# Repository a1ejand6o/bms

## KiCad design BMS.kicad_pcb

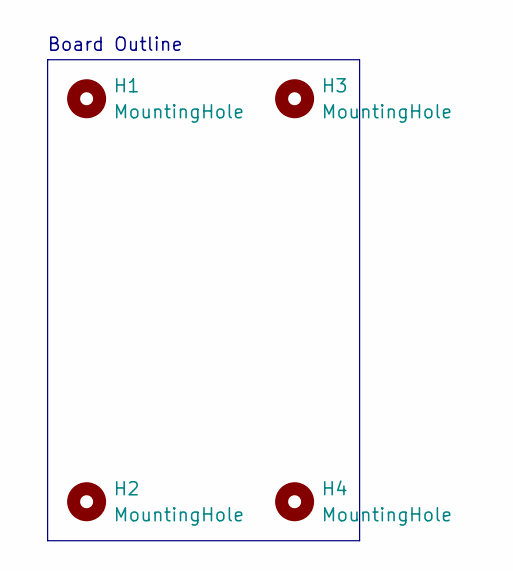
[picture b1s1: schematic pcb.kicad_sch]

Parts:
H1, H2, H3, H4: MountingHole; MountingHole_2.2mm_M2_Pad_TopBottom

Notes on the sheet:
Board Outline

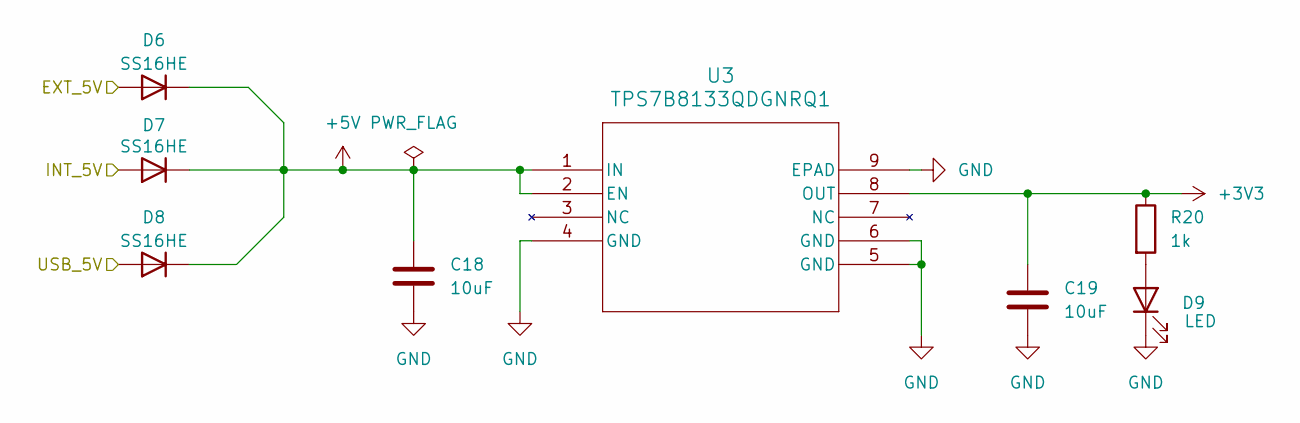
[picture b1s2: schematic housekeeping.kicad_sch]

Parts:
C18, C19: 10uF; C_0805_2012Metric; Mfr P/N GRM21BR61H106KE43L
D6, D7, D8: SS16HE; D_SOD-323F; Mfr P/N SS16HE
D9: LED; LED_0603_1608Metric; Mfr P/N SML-E12P8WT86
R20: 1k; R_0603_1608Metric; Mfr P/N AC0603FR-071KL
U3: TPS7B8133QDGNRQ1; VSSOP8_DGN_TEX; Mfr P/N TPS7B8133QDGNRQ1

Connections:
+3V3: C19.1, R20.1, U3.8 (OUT); also elsewhere on the board
+5V: C18.1, D6.1 (K), D7.1 (K), D8.1 (K), U3.1 (IN), U3.2 (EN); also elsewhere on the board
/main/EXT_5V: D6.2 (A); also elsewhere on the board
/main/INT_5V: D7.2 (A); also elsewhere on the board
/main/V_USB: D8.2 (A); also elsewhere on the board
GND: C18.2, C19.2, D9.1 (K), U3.4 (GND), U3.5 (GND), U3.6 (GND), U3.9 (EPAD); also elsewhere on the board
unnamed: D9.2 (A), R20.2

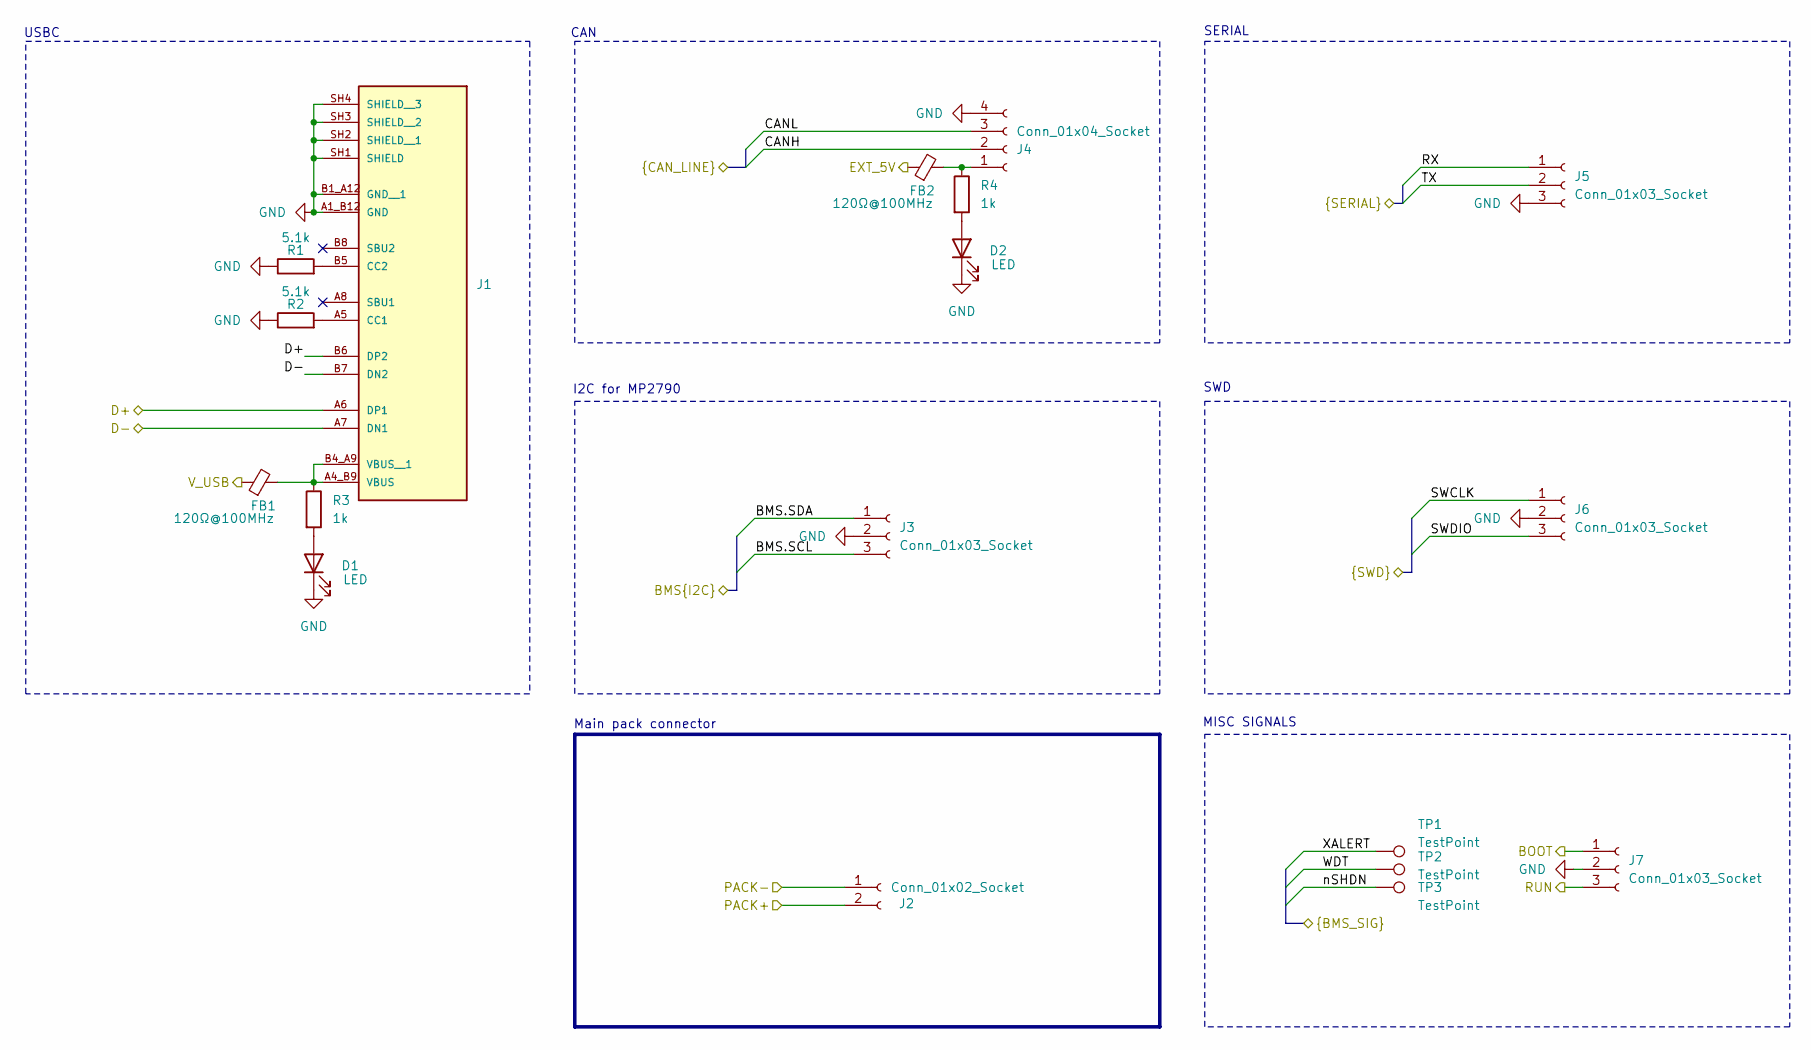
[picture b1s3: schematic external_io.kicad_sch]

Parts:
D1, D2: LED; LED_0603_1608Metric; Mfr P/N SML-E12P8WT86
FB1, FB2: 120Ω@100MHz; L_0603_1608Metric; Mfr P/N BLM18PG121SN1D
J1: UJ20-C-H-G-SMT-1-P16-TR; SAMESKY_UJ20-C-H-G-SMT-1-P16-TR; PARTREV 1.0
J2: Conn_01x02_Socket; AMASS_XT30PW-F_1x02_P2.50mm_Horizontal; Mfr P/N XT30PW-F20.G.Y
J3, J5, J6, J7: Conn_01x03_Socket; PinHeader_1x03_P2.54mm_Vertical; Mfr P/N 2.54-1*3PPin
J4: Conn_01x04_Socket; JST_GH_SM04B-GHS-TB_1x04-1MP_P1.25mm_Horizontal; Mfr P/N SM04B-GHS-TB
R1, R2: 5.1k; R_0603_1608Metric; Mfr P/N AC0603FR-075K1L
R3, R4: 1k; R_0603_1608Metric; Mfr P/N AC0603FR-071KL
TP1, TP2, TP3: TestPoint; Harwin TP; Mfr P/N S2761-46R

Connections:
/main/BMS/PACK-: J2.1; also elsewhere on the board
/main/BMS/SCL: J3.3; also elsewhere on the board
/main/BMS/SDA: J3.1; also elsewhere on the board
/main/CAN/CANH: J4.2; also elsewhere on the board
/main/CAN/CANL: J4.3; also elsewhere on the board
/main/EXT_5V: FB2.1; also elsewhere on the board
/main/PACK+: J2.2; also elsewhere on the board
/main/V_USB: FB1.1; also elsewhere on the board
/main/WDT: TP2.1; also elsewhere on the board
/main/XALERT: TP1.1; also elsewhere on the board
/main/external_io/BOOT: J7.1; also elsewhere on the board
/main/external_io/D+: J1.A6 (DP1), J1.B6 (DP2); also elsewhere on the board
/main/external_io/D-: J1.A7 (DN1), J1.B7 (DN2); also elsewhere on the board
/main/external_io/RUN: J7.3; also elsewhere on the board
/main/external_io/RX: J5.1; also elsewhere on the board
/main/external_io/SWCLK: J6.1; also elsewhere on the board
/main/external_io/SWDIO: J6.3; also elsewhere on the board
/main/external_io/TX: J5.2; also elsewhere on the board
/main/nSHDN: TP3.1; also elsewhere on the board
GND: D1.1 (K), D2.1 (K), J1.A1_B12 (GND), J1.B1_A12 (GND__1), J1.SH1 (SHIELD), J1.SH2 (SHIELD__1), J1.SH3 (SHIELD__2), J1.SH4 (SHIELD__3), J3.2, J4.4, J5.3, J6.2, J7.2, R1.1, R2.1; also elsewhere on the board
unnamed: D1.2 (A), R3.2
unnamed: D2.2 (A), R4.2
unnamed: J1.A5 (CC1), R2.2
unnamed: J1.B5 (CC2), R1.2
unnamed: FB1.2, J1.A4_B9 (VBUS), J1.B4_A9 (VBUS__1), R3.1
unnamed: FB2.2, J4.1, R4.1

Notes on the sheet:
I2C for MP2790
SERIAL
SWD
USBC
Main pack connector
MISC SIGNALS
CAN

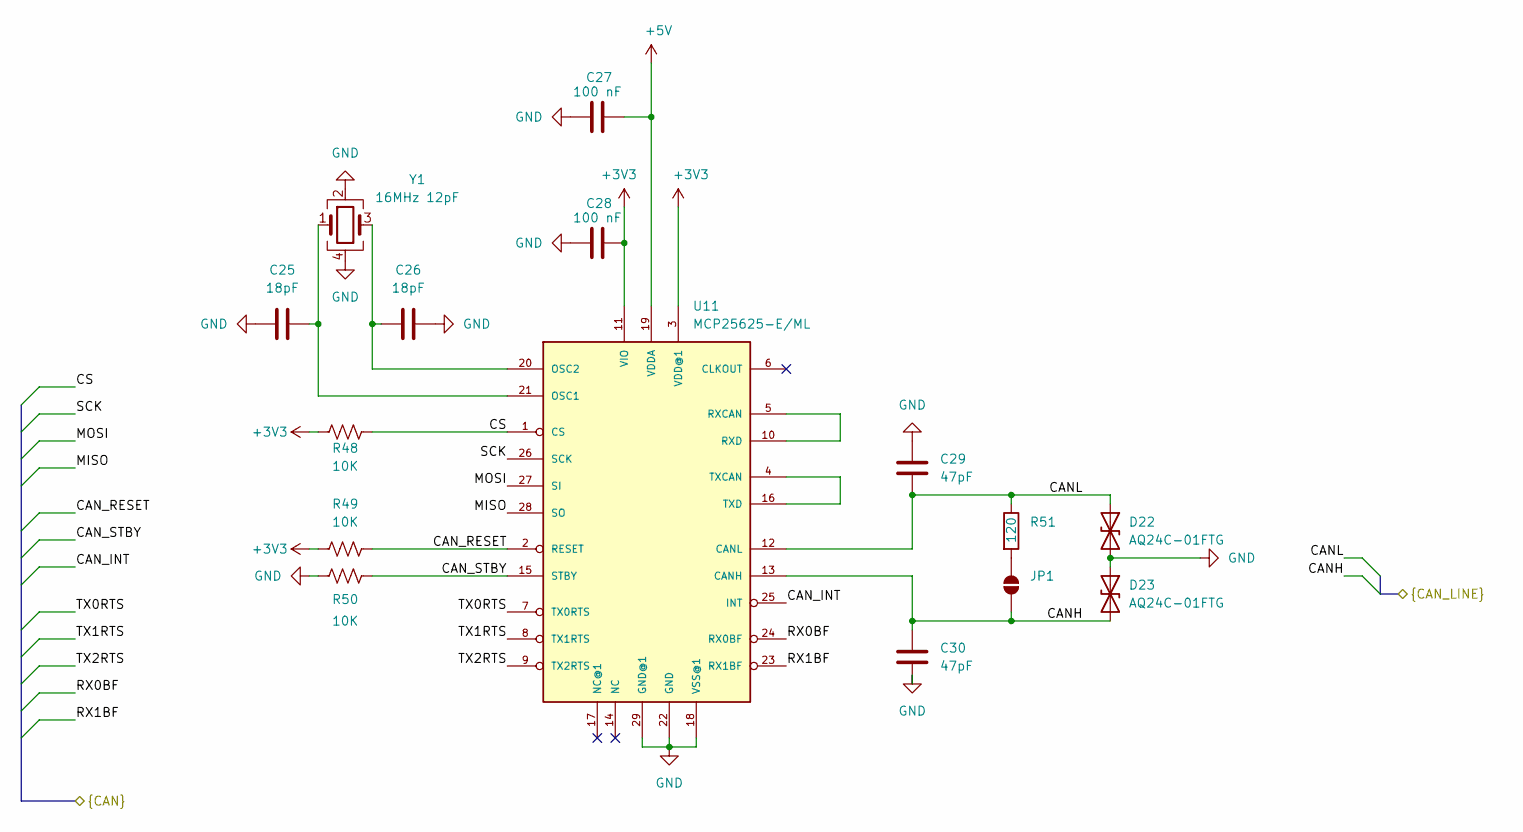
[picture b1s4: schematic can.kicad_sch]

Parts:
C25: 18pF; C_0603_1608Metric; Mfr P/N CL10C180JB8NNNC; LCSC Part C1647
C26: 18pF; C_0603_1608Metric; Mfr P/N CL10C180JB8NNNC
C27, C28: 100 nF; C_0603_1608Metric; Mfr P/N CC0603JRX7R9BB104
C29, C30: 47pF; C_0603_1608Metric; Mfr P/N CL10C470JB8NNNC; LCSC Part C1671
D22, D23: AQ24C-01FTG; D_0805_2012Metric; Mfr P/N AQ24C-01FTG; LCSC Part C315918
JP1: SolderJumper_2_Open; SolderJumper-2_P1.3mm_Open_RoundedPad1.0x1.5mm
R48, R49, R50: 10K; R_0603_1608Metric; Mfr P/N TFCR0603-10W-C-1002FT; LCSC Part C4037161
R51: 120; R_0603_1608Metric; Mfr P/N 0603WAF1200T5E; LCSC Part C22787
U11: MCP25625-E/ML; QFN-28L; Mfr P/N MCP25625-E/ML; LCSC Part C481365
Y1: 16MHz 12pF; Crystal_SMD_2520-4Pin_2.5x2.0mm; Mfr P/N S2216000121080; LCSC Part C426965

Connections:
+3V3: C28.1, R48.1, R49.1, U11.3 (VDD@1), U11.11 (VIO); also elsewhere on the board
+5V: C27.1, U11.19 (VDDA); also elsewhere on the board
/main/CAN/CANH: C30.2, D23.2 (A2), JP1.1 (A), U11.13 (CANH); also elsewhere on the board
/main/CAN/CANL: C29.1, D22.1 (A1), R51.1, U11.12 (CANL); also elsewhere on the board
/main/CAN/CAN_INT: U11.25 (INT); also elsewhere on the board
/main/CAN/CAN_RESET: R49.2, U11.2 (RESET); also elsewhere on the board
/main/CAN/CAN_STBY: R50.1, U11.15 (STBY)
/main/CAN/CS: R48.2, U11.1 (CS); also elsewhere on the board
/main/CAN/MISO: U11.28 (SO); also elsewhere on the board
/main/CAN/MOSI: U11.27 (SI); also elsewhere on the board
/main/CAN/RX0BF: U11.24 (RX0BF)
/main/CAN/RX1BF: U11.23 (RX1BF)
/main/CAN/SCK: U11.26 (SCK); also elsewhere on the board
/main/CAN/TX0RTS: U11.7 (TX0RTS)
/main/CAN/TX1RTS: U11.8 (TX1RTS)
/main/CAN/TX2RTS: U11.9 (TX2RTS)
GND: C25.1, C26.2, C27.2, C28.2, C29.2, C30.1, D22.2 (A2), D23.1 (A1), R50.2, U11.18 (VSS@1), U11.22 (GND), U11.29 (GND@1), Y1.2, Y1.4; also elsewhere on the board
unnamed: JP1.2 (B), R51.2
unnamed: C25.2, U11.21 (OSC1), Y1.1
unnamed: C26.1, U11.20 (OSC2), Y1.3
unnamed: U11.5 (RXCAN), U11.10 (RXD)
unnamed: U11.4 (TXCAN), U11.16 (TXD)

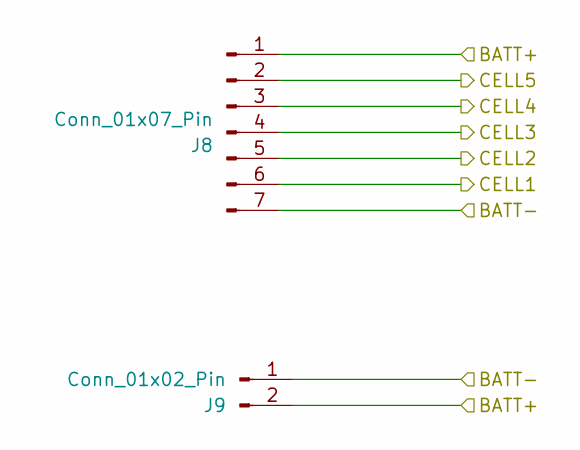
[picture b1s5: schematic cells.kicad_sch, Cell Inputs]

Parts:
J8: Conn_01x07_Pin; JST_XH_S7B-XH-A-1_1x07_P2.50mm_Horizontal; Mfr P/N S7B-XH-A(LF)(SN)
J9: Conn_01x02_Pin; AMASS_XT30PW-M_1x02_P2.50mm_Horizontal; Mfr P/N XT30PW-M30.G.Y

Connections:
/main/BMS/BATT-: J8.7, J9.1; also elsewhere on the board
/main/BMS/C1: J8.6; also elsewhere on the board
/main/BMS/C2: J8.5; also elsewhere on the board
/main/BMS/C3: J8.4; also elsewhere on the board
/main/BMS/C4: J8.3; also elsewhere on the board
/main/BMS/C5: J8.2; also elsewhere on the board
/main/BMS/TOP: J8.1, J9.2; also elsewhere on the board

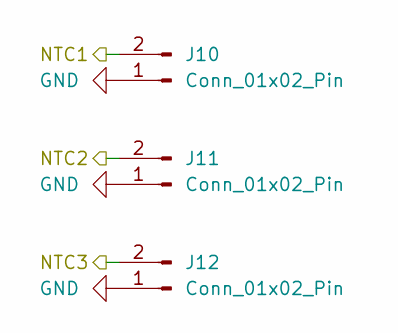
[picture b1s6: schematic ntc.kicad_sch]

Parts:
J10, J11, J12: Conn_01x02_Pin; JST_GH_SM02B-GHS-TB_1x02-1MP_P1.25mm_Horizontal; Mfr P/N SM02B-GHS-TB(LF)(SN)

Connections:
/main/BMS/NTC1: J10.2; also elsewhere on the board
/main/BMS/NTC2: J11.2; also elsewhere on the board
/main/BMS/NTC3: J12.2; also elsewhere on the board
GND: J10.1, J11.1, J12.1; also elsewhere on the board

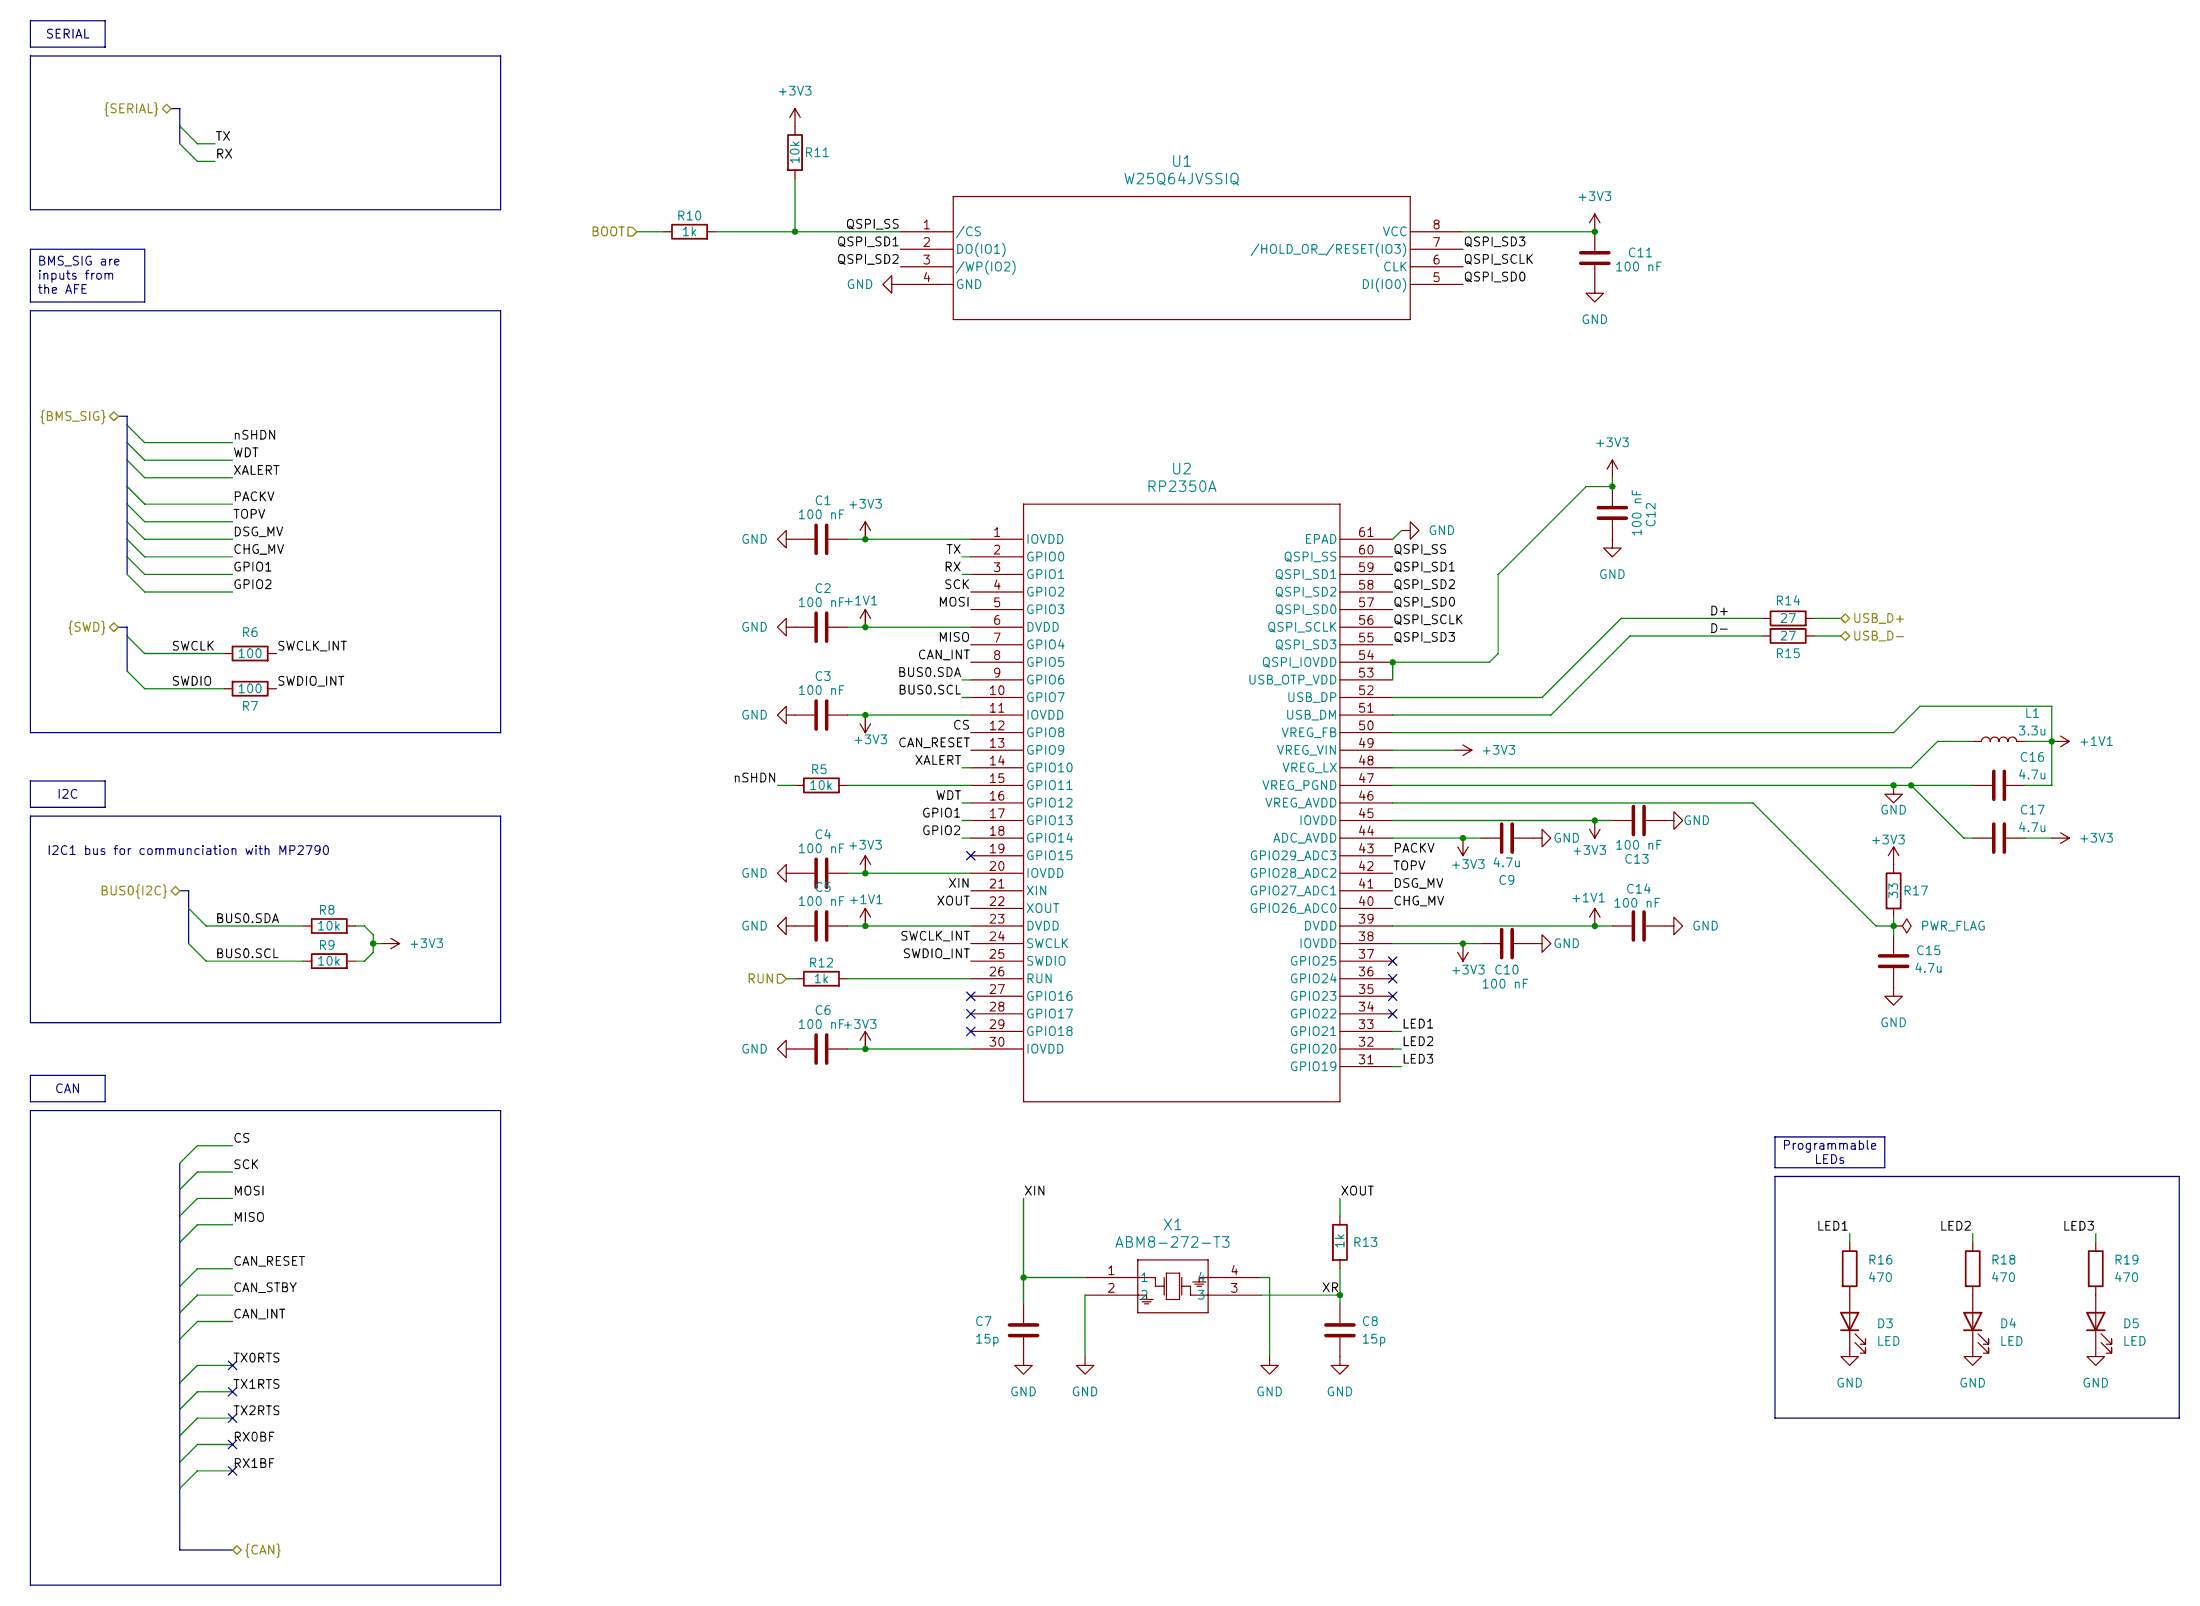
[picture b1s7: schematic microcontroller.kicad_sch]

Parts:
C1, C2, C3, C4, C5, C6, C10, C11, C13, C14: 100 nF; C_0603_1608Metric; Mfr P/N CC0603JRX7R9BB104
C7, C8: 15p; C_0603_1608Metric; Mfr P/N CC0603FRNPO9BN150
C9, C15, C16, C17: 4.7u; C_0603_1608Metric; Mfr P/N GRM188Z71C475KE21D
C12: 100 nF; C_0201_0603Metric; Mfr P/N CC0201KRX7R5BB104
D3, D4, D5: LED; LED_0603_1608Metric; Mfr P/N VLMW1300-GS08
L1: 3.3u; rp_inductor; Mfr P/N AOTA-B201610S3R3-101-T
R5, R8, R9, R11: 10k; R_0603_1608Metric; Mfr P/N RT0603BRD0710KL
R6, R7: 100; R_0603_1608Metric; Mfr P/N RT0603BRD07100RL
R10, R12: 1k; R_0603_1608Metric; Mfr P/N RC0603FR-071KL
R13: 1k; R_0603_1608Metric; Mfr P/N AC0603FR-071KL
R14, R15: 27; R_0201_0603Metric; Mfr P/N RT0603BRD0727RL
R16, R18, R19: 470; R_0603_1608Metric; Mfr P/N RC0603FR-07470RL
R17: 33; R_0603_1608Metric; Mfr P/N RK73H1JTTD33R0F
U1: W25Q64JVSSIQ; SOIC-8_5P28X5P28_WIN; Mfr P/N W25Q64JVSSIQ
U2: RP2350A; QFN-60-1EP_7x7mm_P0.4mm_EP3.4x3.4mm_ThermalVias; Mfr P/N SC1511(13)-A4
X1: ABM8-272-T3; ABM8-272-T3_ABR; Mfr P/N ABM8-272-T3

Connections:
+1V1: C2.1, C5.1, C14.1, C16.2, L1.2, U2.6 (DVDD), U2.23 (DVDD), U2.39 (DVDD), U2.50 (VREG_FB)
+3V3: C1.1, C3.1, C4.1, C6.1, C9.1, C10.1, C11.2, C12.2, C13.1, C17.1, R8.2, R9.2, R11.1, R17.1, U1.8 (VCC), U2.1 (IOVDD), U2.11 (IOVDD), U2.20 (IOVDD), U2.30 (IOVDD), U2.38 (IOVDD), U2.44 (ADC_AVDD), U2.45 (IOVDD), U2.49 (VREG_VIN), U2.53 (USB_OTP_VDD), U2.54 (QSPI_IOVDD); also elsewhere on the board
/main/BMS/SCL: R9.1, U2.10 (GPIO7); also elsewhere on the board
/main/BMS/SDA: R8.1, U2.9 (GPIO6); also elsewhere on the board
/main/CAN/CAN_INT: U2.8 (GPIO5); also elsewhere on the board
/main/CAN/CAN_RESET: U2.13 (GPIO9); also elsewhere on the board
/main/CAN/CS: U2.12 (GPIO8); also elsewhere on the board
/main/CAN/MISO: U2.7 (GPIO4); also elsewhere on the board
/main/CAN/MOSI: U2.5 (GPIO3); also elsewhere on the board
/main/CAN/SCK: U2.4 (GPIO2); also elsewhere on the board
/main/CHG_MV: U2.40 (GPIO26_ADC0)
/main/DSG_MV: U2.41 (GPIO27_ADC1)
/main/GPIO1: U2.17 (GPIO13); also elsewhere on the board
/main/GPIO2: U2.18 (GPIO14); also elsewhere on the board
/main/PACKV: U2.43 (GPIO29_ADC3)
/main/TOPV: U2.42 (GPIO28_ADC2)
/main/WDT: U2.16 (GPIO12); also elsewhere on the board
/main/XALERT: U2.14 (GPIO10); also elsewhere on the board
/main/external_io/BOOT: R10.1; also elsewhere on the board
/main/external_io/D+: R14.2; also elsewhere on the board
/main/external_io/D-: R15.1; also elsewhere on the board
/main/external_io/RUN: R12.1; also elsewhere on the board
/main/external_io/RX: U2.3 (GPIO1); also elsewhere on the board
/main/external_io/SWCLK: R6.1; also elsewhere on the board
/main/external_io/SWDIO: R7.2; also elsewhere on the board
/main/external_io/TX: U2.2 (GPIO0); also elsewhere on the board
/main/microcontroller/D+: R14.1, U2.52 (USB_DP)
/main/microcontroller/D-: R15.2, U2.51 (USB_DM)
/main/microcontroller/LED1: R16.1, U2.33 (GPIO21)
/main/microcontroller/LED2: R18.1, U2.32 (GPIO20)
/main/microcontroller/LED3: R19.1, U2.31 (GPIO19)
/main/microcontroller/QSPI_SCLK: U1.6 (CLK), U2.56 (QSPI_SCLK)
/main/microcontroller/QSPI_SD0: U1.5 (DI(IO0)), U2.57 (QSPI_SD0)
/main/microcontroller/QSPI_SD1: U1.2 (DO(IO1)), U2.59 (QSPI_SD1)
/main/microcontroller/QSPI_SD2: U1.3 (/WP(IO2)), U2.58 (QSPI_SD2)
/main/microcontroller/QSPI_SD3: U1.7 (/HOLD_OR_/RESET(IO3)), U2.55 (QSPI_SD3)
/main/microcontroller/QSPI_SS: R10.2, R11.2, U1.1 (/CS), U2.60 (QSPI_SS)
/main/microcontroller/SWCLK_INT: R6.2, U2.24 (SWCLK)
/main/microcontroller/SWDIO_INT: R7.1, U2.25 (SWDIO)
/main/microcontroller/XIN: C7.1, U2.21 (XIN), X1.1
/main/microcontroller/XOUT: R13.1, U2.22 (XOUT)
/main/microcontroller/XR: C8.2, R13.2, X1.3
/main/nSHDN: R5.1; also elsewhere on the board
GND: C1.2, C2.2, C3.2, C4.2, C5.2, C6.2, C7.2, C8.1, C9.2, C10.2, C11.1, C12.1, C13.2, C14.2, C15.2, C16.1, C17.2, D3.1 (K), D4.1 (K), D5.1 (K), U1.4 (GND), U2.47 (VREG_PGND), U2.61 (EPAD), X1.2, X1.4; also elsewhere on the board
unnamed: D3.2 (A), R16.2
unnamed: D4.2 (A), R18.2
unnamed: D5.2 (A), R19.2
unnamed: R5.2, U2.15 (GPIO11)
unnamed: R12.2, U2.26 (RUN)
unnamed: C15.1, R17.2, U2.46 (VREG_AVDD)
unnamed: L1.1, U2.48 (VREG_LX)

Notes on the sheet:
I2C1 bus for communciation with MP2790
BMS_SIG are inputs from the AFE
I2C
CAN
SERIAL
Programmable LEDs
